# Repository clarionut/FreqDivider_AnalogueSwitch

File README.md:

# Frequency Divider / Analogue Switch

This repository contains details of synthesiser module providing a 4-stage frequency divider linked to three 2-in 2-out analogue changeover switches.

The frequency divider comprises two CD4027B Dual J-K flip-flops with each stage wired as a T-type flip-flop. Each stage toggles its state on the rising edge of its clock signal, converting the incoming pulse train into a square wave of half the incoming frequency. By default the output of each stage is normalled to the input of the next, so a single clock input can give four outputs of 1/2, 1/4, 1/8 and 1/16 the incoming frequency. Multiple input clocks can be processed using the input jacks on the later divider stages, e.g to divide one clock by 2 and a second clock by 2, 4 & 8. The outputs of each stage are 0-9V square waves.

The module also includes three 'two-pole changeover' analogue switches based on two CD4053B 3-channel mux/demux chips. The CD4053Bs are powered by +12 & -6V and consequently can handle Eurorack standard voltages of ±5V or 0-10V (with protection against out-of-range voltages) and will work with both CVs and audio-rate signals. Each of the virtual changeover switches can be connected to any of the four frequency divider stages and multiple switches can be connected to the same divider output. I used red/white bicolor LEDs to indicate the state of each changeover switch; when the control input to a switch is high its LED is white and the two inputs connect straight to the outputs and when low the LED is red and the inputs cross over to the outputs.

The original inspiration for this module was to provide a means of using my [ADCequencer](https://github.com/clarionut/ADCequencer) 8-step 2-channel sequencer as a 16-step 1-channel sequencer. Passing the two analogue outputs of the sequencer through a changeover switch clocked at 1/16 the speed of the sequencer swaps between the two outputs every 8 steps creating a 16 step sequence. Interesting variations can also be introduced by changing the relative phasing of the sequencer and the analogue switch. The frequency divider has a manual clock input to allow such changes on the fly.

##Hardware Notes

My synth is Eurorack format and to save space I used small 2-pole 4-way slide switches as the selectors connecting the analogue switches to the divider output stages. Unfortunately these are make-before-break which can cause glitching when switching on the fly. If you build in a larger format like Kosmo it would be better to use small break-before-make rotary switches for these selectors. If you're forced to use make-before-break switches it's best to set them up when all the divider outputs are in the same (high or low) state. Note that it's also extremely fiddly wiring the connections between the switch/LED sub-boards if you use the small slide switches!

##KiCad files

The schematic and PCB files are provided in KiCad 7 format and as PDFs. Note that the front copper ground plane is excluded from the board PDF for clarity but is present in the KiCad files. The schematic uses some custom symbols and the PCB some custom footprints, so you will need to download my [custom KiCad libraries](https://github.com/clarionut/kiCad_libraries) and tell KiCad where to find them. The PCB file is intended to be processed by the KiCad 'Round Tracks' plugin but will work perfectly well without. I've included the Gerber files but these will only be useful if you mount the PCB on brackets behind and perpendicular to the front panel.

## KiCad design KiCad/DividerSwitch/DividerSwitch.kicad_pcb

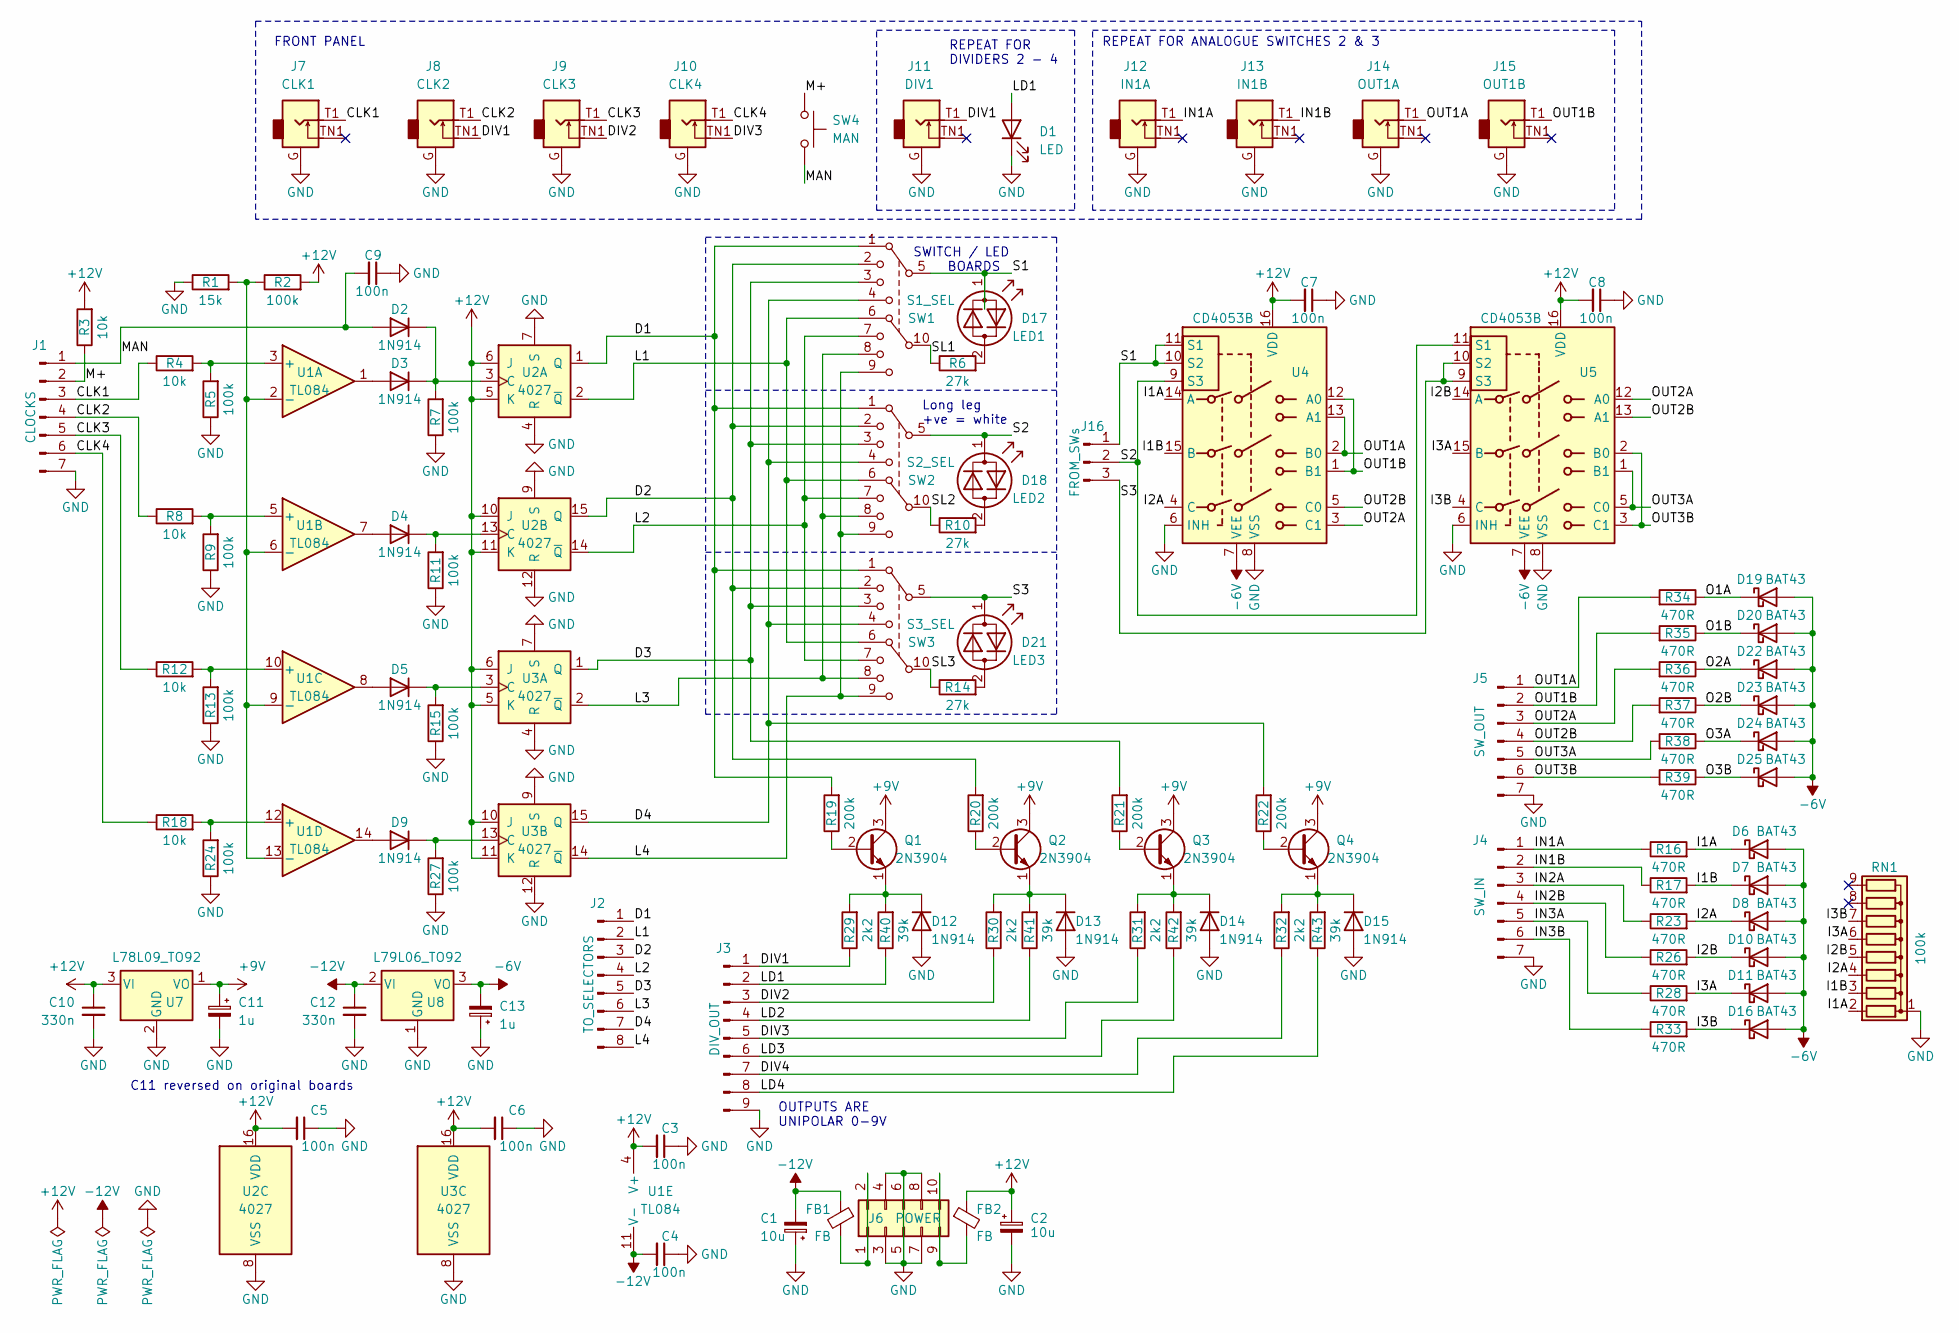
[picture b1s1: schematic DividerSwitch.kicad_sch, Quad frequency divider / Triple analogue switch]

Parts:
C1, C2: 10u; CP_Radial_D5.0mm_P2.50mm
C3, C4, C5, C6, C7, C8, C9: 100n; C_Disc_D4.3mm_W1.9mm_P5.00mm
C10, C12: 330n; C_Disc_D4.3mm_W1.9mm_P5.00mm
C11, C13: 1u; CP_Radial_D5.0mm_P2.50mm
D1: LED
D2, D3, D4, D5, D9, D12, D13, D14, D15: 1N914; D_DO-35_SOD27_P7.62mm_Horizontal
D6, D7, D8, D10, D11, D16, D19, D20, D22, D23, D24, D25: BAT43; D_DO-35_SOD27_P7.62mm_Horizontal
D17: LED1; LED_D5.0mm
D18: LED2; LED_D5.0mm
D21: LED3; LED_D5.0mm
FB1, FB2: FB; L_Axial_L5.3mm_D2.2mm_P7.62mm_Horizontal_Vishay_IM-1
J1: CLOCKS; PinHeader_1x07_P2.54mm_Vertical
J2: TO_SELECTORS; PinHeader_1x08_P2.54mm_Vertical
J3: DIV_OUT; PinHeader_1x09_P2.54mm_Vertical
J4: SW_IN; PinHeader_1x07_P2.54mm_Vertical
J5: SW_OUT; PinHeader_1x07_P2.54mm_Vertical
J6: POWER; Power_2x05
J7: CLK1
J8: CLK2
J9: CLK3
J10: CLK4
J11: DIV1
J12: IN1A
J13: IN1B
J14: OUT1A
J15: OUT1B
J16: FROM_SWs; PinHeader_1x03_P2.54mm_Vertical
Q1, Q2, Q3, Q4: 2N3904; TO-92_HandSolder
R1: 15k; R_Axial_DIN0204_L3.6mm_D1.6mm_P7.62mm_Horizontal
R2, R5, R7, R9, R11, R13, R15, R24, R27: 100k; R_Axial_DIN0204_L3.6mm_D1.6mm_P7.62mm_Horizontal
R3, R4, R8, R12, R18: 10k; R_Axial_DIN0204_L3.6mm_D1.6mm_P7.62mm_Horizontal
R6, R10, R14: 27k; R_Axial_DIN0204_L3.6mm_D1.6mm_P7.62mm_Horizontal
R16, R17, R23, R26, R28, R33, R34, R35, R36, R37, R38, R39: 470R; R_Axial_DIN0204_L3.6mm_D1.6mm_P7.62mm_Horizontal
R19, R20, R21, R22: 200k; R_Axial_DIN0204_L3.6mm_D1.6mm_P7.62mm_Horizontal
R29, R30, R31, R32: 2k2; R_Axial_DIN0204_L3.6mm_D1.6mm_P7.62mm_Horizontal
R40, R41, R42, R43: 39k; R_Axial_DIN0204_L3.6mm_D1.6mm_P7.62mm_Horizontal
RN1: 100k; R_Array_SIP9
SW1: S1_SEL; SW_DP4T_slide
SW2: S2_SEL; SW_DP4T_slide
SW3: S3_SEL; SW_DP4T_slide
SW4: MAN
U1: TL084; DIP-14_W7.62mm_Socket
U2, U3: 4027; DIP-16_W7.62mm_Socket
U4, U5: CD4053B; DIP-16_W7.62mm_Socket
U7: L78L09_TO92; TO-92_HandSolder
U8: L79L06_TO92; TO-92_HandSolder

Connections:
+9V: C11.1, Q1.3 (C), Q2.3 (C), Q3.3 (C), Q4.3 (C), U7.1 (VO)
+12V: C2.1, C3.2, C5.2, C6.2, C7.2, C8.2, C10.1, FB2.1, R2.2, R3.2, U1.4 (V+), U2.5 (K), U2.6 (J), U2.10 (J), U2.11 (K), U2.16 (VDD), U3.5 (K), U3.6 (J), U3.10 (J), U3.11 (K), U3.16 (VDD), U4.16 (VDD), U5.16 (VDD), U7.3 (VI)
-6V: C13.2, D6.2 (A), D7.2 (A), D8.2 (A), D10.2 (A), D11.2 (A), D16.2 (A), D19.2 (A), D20.2 (A), D22.2 (A), D23.2 (A), D24.2 (A), D25.2 (A), U4.7 (VEE), U5.7 (VEE), U8.3 (VO)
-12V: C1.2, C4.2, C12.1, FB1.1, U1.11 (V-), U8.2 (VI)
/CLK1: J1.3, J7.T1, R4.1
/CLK2: J1.4, J8.T1, R8.1
/CLK3: J1.5, J9.T1, R12.1
/CLK4: J1.6, J10.T1, R18.1
/D1: J2.1, R19.2, SW1.1, SW2.1, SW3.1, U2.1 (Q)
/D2: J2.3, R20.2, SW1.2, SW2.2, SW3.2, U2.15 (Q)
/D3: J2.5, R21.2, SW1.3, SW2.3, SW3.3, U3.1 (Q)
/D4: J2.7, R22.2, SW1.4, SW2.4, SW3.4, U3.15 (Q)
/DIV1: J3.1, J8.TN1, J11.T1, R29.1
/DIV2: J3.3, J9.TN1, R30.1
/DIV3: J3.5, J10.TN1, R31.1
/DIV4: J3.7, R32.1
/I1A: D6.1 (K), R16.2, RN1.2 (R1), U4.14 (A)
/I1B: D7.1 (K), R17.2, RN1.3 (R2), U4.15 (B)
/I2A: D8.1 (K), R23.2, RN1.4 (R3), U4.4 (C)
/I2B: D10.1 (K), R26.2, RN1.5 (R4), U5.14 (A)
/I3A: D11.1 (K), R28.2, RN1.6 (R5), U5.15 (B)
/I3B: D16.1 (K), R33.2, RN1.7 (R6), U5.4 (C)
/IN1A: J4.1, J12.T1, R16.1
/IN1B: J4.2, J13.T1, R17.1
/IN2A: J4.3, R23.1
/IN2B: J4.4, R26.1
/IN3A: J4.5, R28.1
/IN3B: J4.6, R33.1
/L1: J2.2, SW1.6, SW2.6, SW3.6, U2.2 (~Q)
/L2: J2.4, SW1.7, SW2.7, SW3.7, U2.14 (~Q)
/L3: J2.6, SW1.8, SW2.8, SW3.8, U3.2 (~Q)
/L4: J2.8, SW1.9, SW2.9, SW3.9, U3.14 (~Q)
/LD1: D1.2 (A), J3.2, R40.1
/LD2: J3.4, R41.1
/LD3: J3.6, R42.1
/LD4: J3.8, R43.1
/M+: J1.2, R3.1, SW4.1
/MAN: C9.2, D2.2 (A), J1.1, SW4.2
/O1A: D19.1 (K), R34.1
/O1B: D20.1 (K), R35.1
/O2A: D22.1 (K), R36.1
/O2B: D23.1 (K), R37.1
/O3A: D24.1 (K), R38.1
/O3B: D25.1 (K), R39.1
/OUT1A: J5.1, J14.T1, R34.2, U4.2 (B0), U4.13 (A1)
/OUT1B: J5.2, J15.T1, R35.2, U4.1 (B1), U4.12 (A0)
/OUT2A: J5.3, R36.2, U4.3 (C1), U5.12 (A0)
/OUT2B: J5.4, R37.2, U4.5 (C0), U5.13 (A1)
/OUT3A: J5.5, R38.2, U5.1 (B1), U5.5 (C0)
/OUT3B: J5.6, R39.2, U5.2 (B0), U5.3 (C1)
/S1: D17.1 (KA), J16.1, SW1.5, U4.10 (S2), U4.11 (S1)
/S2: D18.1 (KA), J16.2, SW2.5, U4.9 (S3), U5.11 (S1)
/S3: D21.1 (KA), J16.3, SW3.5, U5.9 (S3), U5.10 (S2)
/SL1: R6.1, SW1.10
/SL2: R10.1, SW2.10
/SL3: R14.1, SW3.10
GND: C1.1, C2.2, C3.1, C4.1, C5.1, C6.1, C7.1, C8.1, C9.1, C10.2, C11.2, C12.2, C13.1, D1.1 (K), D12.2 (A), D13.2 (A), D14.2 (A), D15.2 (A), J1.7, J3.9, J4.7, J5.7, J6.3, J6.4, J6.5, J6.6, J6.7, J6.8, J7.G, J8.G, J9.G, J10.G, J11.G, J12.G, J13.G, J14.G, J15.G, R1.1, R5.1, R7.1, R9.1, R11.1, R13.1, R15.1, R24.1, R27.1, RN1.1 (common), U2.4 (R), U2.7 (S), U2.8 (VSS), U2.9 (S), U2.12 (R), U3.4 (R), U3.7 (S), U3.8 (VSS), U3.9 (S), U3.12 (R), U4.6 (INH), U4.8 (VSS), U5.6 (INH), U5.8 (VSS), U7.2 (GND), U8.1 (GND)
unnamed: D2.1 (K), D3.1 (K), R7.2, U2.3 (C)
unnamed: D3.2 (A), U1.1
unnamed: D4.2 (A), U1.7
unnamed: D4.1 (K), R11.2, U2.13 (C)
unnamed: D5.2 (A), U1.8
unnamed: D5.1 (K), R15.2, U3.3 (C)
unnamed: D9.2 (A), U1.14
unnamed: D9.1 (K), R27.2, U3.13 (C)
unnamed: D12.1 (K), Q1.1 (E), R29.2, R40.2
unnamed: D13.1 (K), Q2.1 (E), R30.2, R41.2
unnamed: D14.1 (K), Q3.1 (E), R31.2, R42.2
unnamed: D15.1 (K), Q4.1 (E), R32.2, R43.2
unnamed: D17.2 (AK), R6.2
unnamed: D18.2 (AK), R10.2
unnamed: D21.2 (AK), R14.2
unnamed: FB1.2, J6.1, J6.2
unnamed: FB2.2, J6.9, J6.10
unnamed: Q1.2 (B), R19.1
unnamed: Q2.2 (B), R20.1
unnamed: Q3.2 (B), R21.1
unnamed: Q4.2 (B), R22.1
unnamed: R4.2, R5.2, U1.3 (+)
unnamed: R1.2, R2.1, U1.2 (-), U1.6 (-), U1.9 (-), U1.13 (-)
unnamed: R8.2, R9.2, U1.5 (+)
unnamed: R12.2, R13.2, U1.10 (+)
unnamed: R18.2, R24.2, U1.12 (+)

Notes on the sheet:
C11 reversed on original boards
REPEAT FOR ANALOGUE SWITCHES 2 & 3
FRONT PANEL
SWITCH / LED BOARDS
Long leg +ve = white
OUTPUTS ARE UNIPOLAR 0-9V
REPEAT FOR DIVIDERS 2 - 4

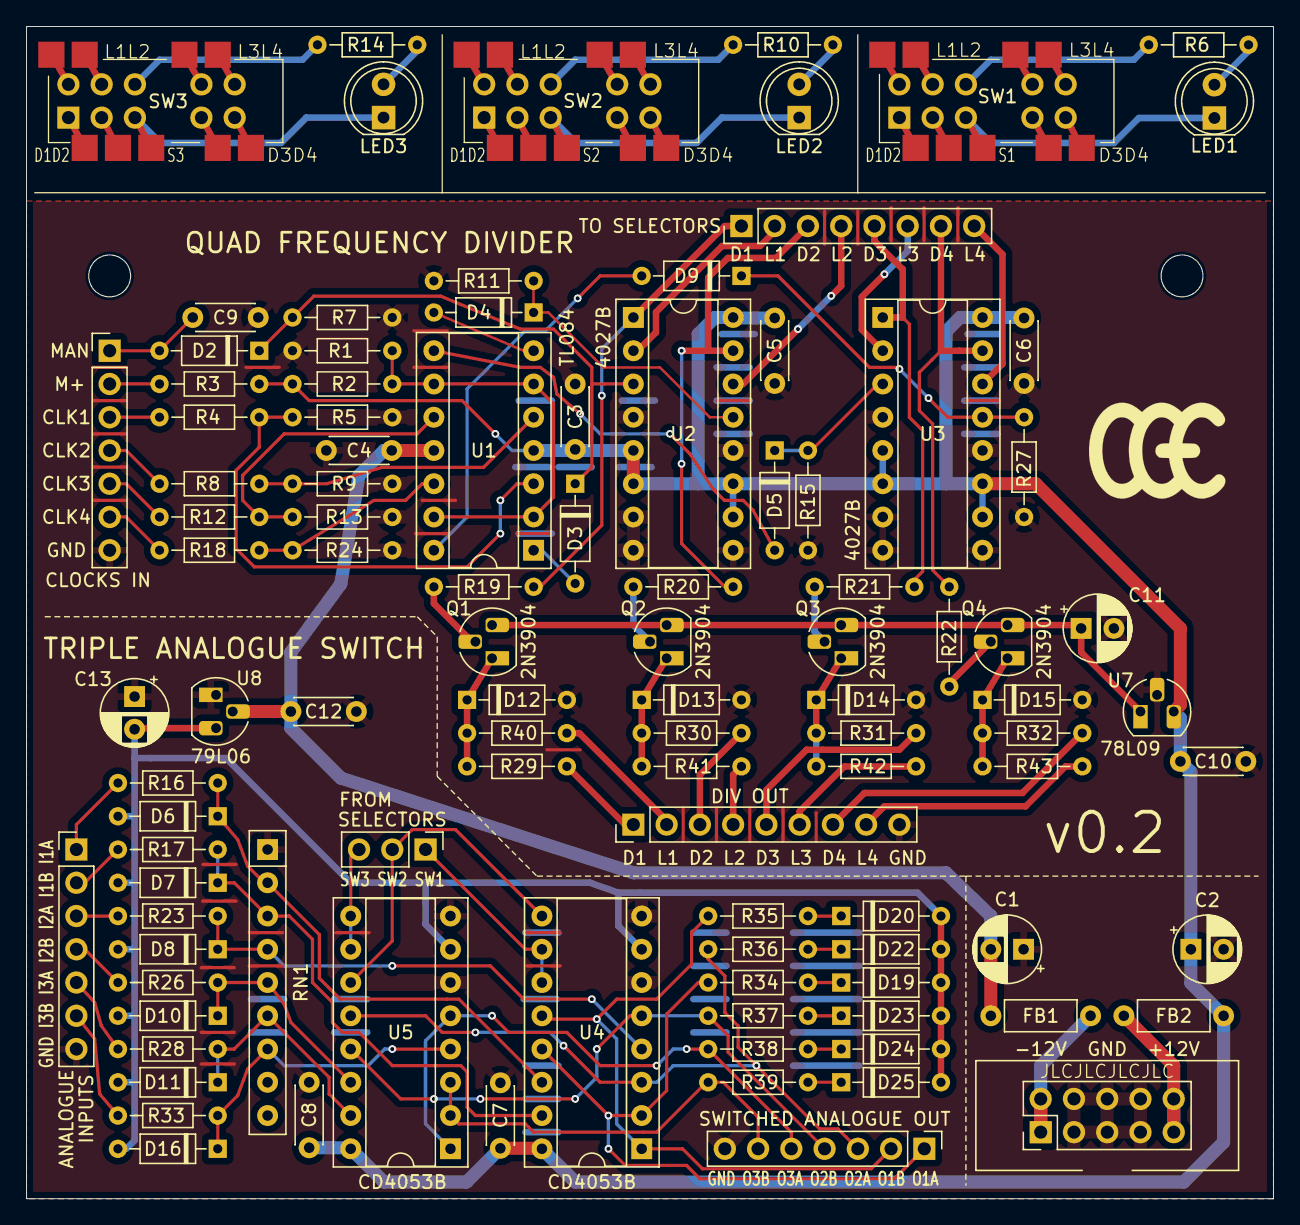
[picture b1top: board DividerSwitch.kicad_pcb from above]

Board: 2 copper layers, 95.2 x 89.5 mm, 103 parts (0 on the bottom side), 83 nets.

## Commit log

2024-11-14 Create temp
2024-11-14 Create tmp
